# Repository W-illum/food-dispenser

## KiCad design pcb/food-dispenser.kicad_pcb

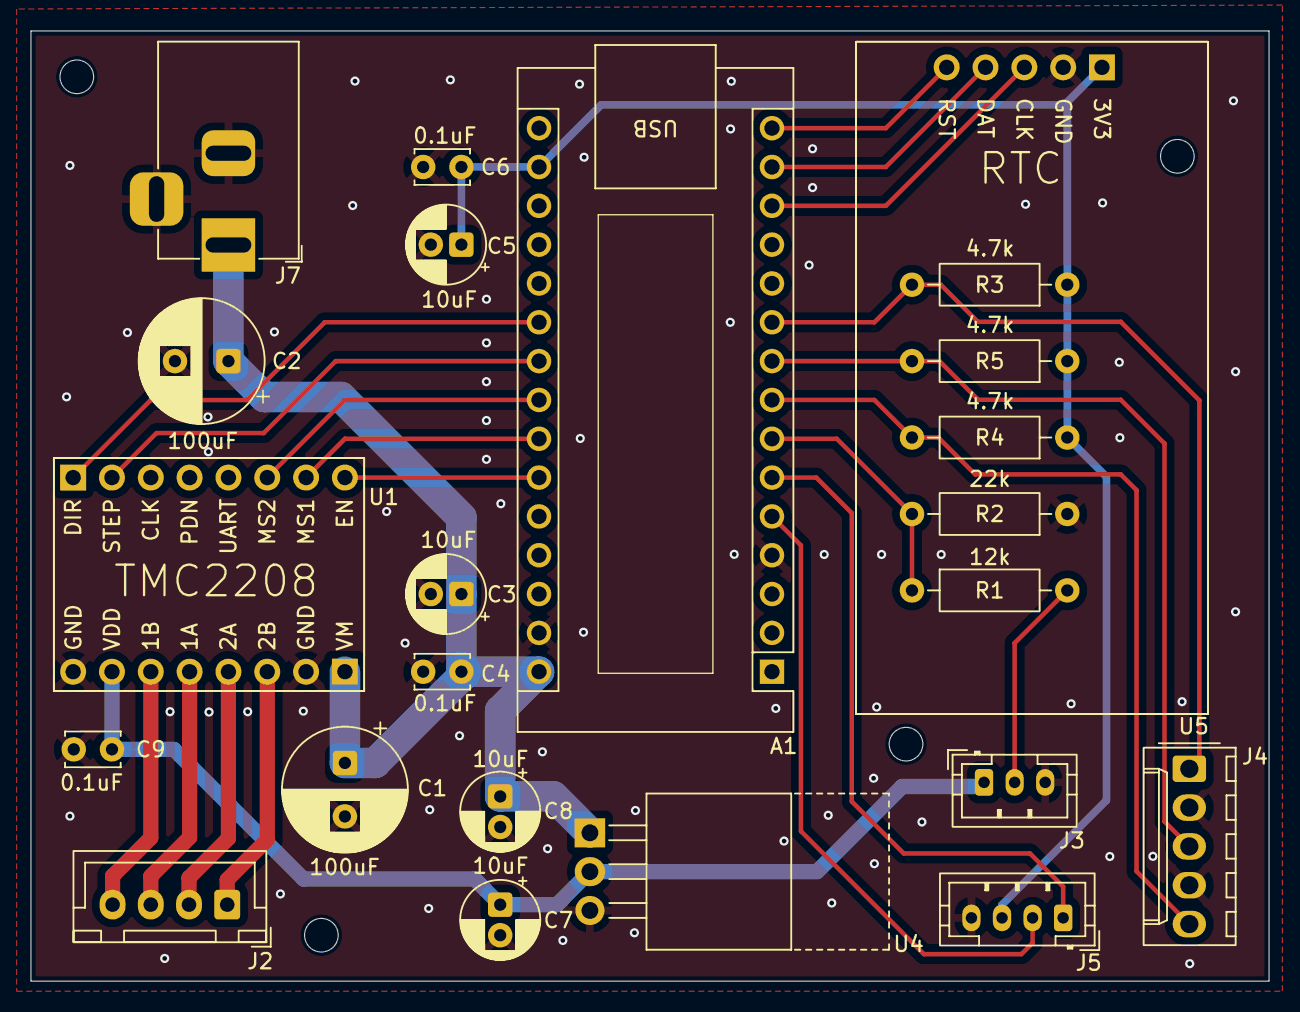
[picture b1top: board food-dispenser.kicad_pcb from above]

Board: 2 copper layers, 81.0 x 62.2 mm, 23 parts (0 on the bottom side), 23 nets.

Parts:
A1: Arduino_Nano_ESP32; Arduino_Nano
C1, C2: 100uF; CP_Radial_D8.0mm_P3.50mm
C3, C5, C7, C8: 10uF; CP_Radial_D5.0mm_P2.00mm
C4, C6, C9: 0.1uF; C_Disc_D3.4mm_W2.1mm_P2.50mm
J2: Stepper_conn; JST_XH_B4B-XH-A_1x04_P2.50mm_Vertical
J3: Lidar_conn; JST_PH_B3B-PH-K_1x03_P2.00mm_Vertical
J4: Encoder_conn; Molex_KK-254_AE-6410-05A_1x05_P2.54mm_Vertical
J5: LCD_conn; JST_PH_B4B-PH-K_1x04_P2.00mm_Vertical
J7: DC Jack Mountingpin; BarrelJack_Horizontal
R1: 12k; R_Axial_DIN0207_L6.3mm_D2.5mm_P10.16mm_Horizontal
R2: 22k; R_Axial_DIN0207_L6.3mm_D2.5mm_P10.16mm_Horizontal
R3, R4, R5: 4.7k; R_Axial_DIN0207_L6.3mm_D2.5mm_P10.16mm_Horizontal
U1: MKS TMC2208; MKS TMC_2208 Module
U4: LD1085; TO-220-3_Horizontal_TabUp
U5: RTC_Module (DS1302); RTC Module(DS1302)

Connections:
+3V3: A1.17 (3V3), C5.1, C6.1, J5.3, R3.1, R4.1, R5.1, U5.1 (3V3)
+5V: C7.1, C9.2, J3.1, U1.7 (VDD), U4.2 (OUT)
+12V: A1.30 (VIN), C1.1, C2.1, C3.1, C4.1, C8.1, J7.1, U1.1 (VM), U4.1 (IN)
/1A: J2.3, U1.5 (1A)
/1B: J2.4, U1.6 (1B)
/2A: J2.2, U1.4 (2A)
/2B: J2.1, U1.3 (2B)
/A: A1.8 (D5), J4.5, R4.2
/B: A1.9 (D6), J4.3, R5.2
/CLK: A1.13 (D10/CS), U5.3 (CLK)
/D7: A1.7 (D4), R1.1, R2.2
/DAT: A1.14 (D11/COPI), U5.4 (DAT_IN_OUT)
/DIR: A1.21 (A2), U1.16 (DIR)
/EN: A1.25 (A6), U1.9 (EN)
/LIDAR_PWM: J3.2, R1.2
/MS1: A1.24 (SCL/A5), U1.10 (MS1)
/MS2: A1.23 (SDA/A4), U1.11 (MS2)
/RST: A1.15 (D12/CIPO), U5.5 (RST)
/SCL: A1.6 (D3), J5.1
/SDA: A1.5 (D2), J5.2
/STEP: A1.22 (A3), U1.15 (STEP)
/SW1: A1.10 (D7), J4.1, R3.2
GND: A1.4 (GND), A1.29 (GND), C1.2, C2.2, C3.2, C4.2, C5.2, C6.2, C7.2, C8.2, C9.1, J3.3, J4.2, J4.4, J5.4, J7.2, J7.3 (MountPin), R2.1, U1.2 (GND), U1.8 (GND), U4.3 (GND), U5.2 (GND)

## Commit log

2026-02-02 added lcd lib
2026-02-02 Started on Rotary Encoder, needs better debounce
2026-02-02 added env for win / linux
2026-02-02 minimized debounce on rotation and button (not 100% perfect)
2026-02-04 fixed states, no bouncing arround
2026-02-04 simple no timer/interrupt test for motor
2026-02-05 changed to esp pins instead of arduino
2026-02-05 timer interrupts on motor
2026-02-05 consistent namings etc
2026-02-05 working stepper + encoder
2026-02-07 tested lcd, motor and lidar (lidar needs 5V)
2026-02-08 only enable motor driver when we need it
2026-02-12 Added feeder and schedule class
2026-02-12 Added Menu class, using LCD functions, reacting on encoder click and rotation
2026-02-12 simple main only calling on update in Feeder
2026-02-12 removed src folder
2026-03-05 added datasheets to project
2026-03-05 added rtc lib
2026-03-05 moved layout to datasheet
2026-03-05 removed internal pullup and replaced with external ones
2026-03-05 made a more generic time struct
2026-03-05 added rtc and tested lidar code
2026-03-05 changed the time struct to more generic one
2026-03-05 added clock settings etc to lcd screen
2026-03-06 added schematic and pcb picture
2026-03-06 fix png
2026-03-07 moved sda, scl pins
2026-03-26 Added feeder logic and lidar (Version 1), TODO: test motor rotation and food amount values
2026-03-26 fixed minor mistakes
2026-05-02 removed pull_mode comments, physical pull ups are used
2026-05-02 Added const to render functions
2026-05-02 cleaned up
2026-05-02 Renamed events to be more generic for other input types like BLE
2026-05-02 renamed time.h to not clash with ESP time.h
2026-05-02 added ble support as input
2026-05-02 moved rtc to libdeps and sparkfun to gitmodule
2026-05-02 project description
2026-05-02 pcb files
